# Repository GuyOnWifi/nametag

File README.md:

# Strawberry Badge

A little strawberry themed badge, with a microcontroller to control a bunch of LEDs. Twenty LEDs controlled by 5 GPIOs, what can go wrong? 

## BOM

| Designator | Footprint | Quantity | Value | LCSC Part # |
| --- | --- | --- | --- | --- |
| BT1 | BatteryHolder_Keystone_3034_1x20mm | 1 | Battery_Cell | C70376 |
| C1 | 0603 | 1 | 10pF | |
| C2 | 0603 | 1 | 100nF | |
| D1, D2, D3, D4, D5, D6, D7, D8, D9, D10, D12, D13, D15, D16, D17, D18, D19, D22 | 1206 | 18 | LED | |
| J1 | PinHeader_1x06_P2.54mm_Vertical | 1 | Conn_01x06_Pin | |
| R1, R2, R3, R4, R5 | 1206 | 5 | 330R | |
| R6 | 0603 | 1 | 10k | |
| U1 | QFN8P50_160X160X50L40X20N | 1 | NT3H2111W0FHK | C710403 |
| U2 | SOIC-8_5.3x5.3mm_P1.27mm | 1 | ATtiny85-20S | C89852 |

##

Slack Username: `Eason Huang`

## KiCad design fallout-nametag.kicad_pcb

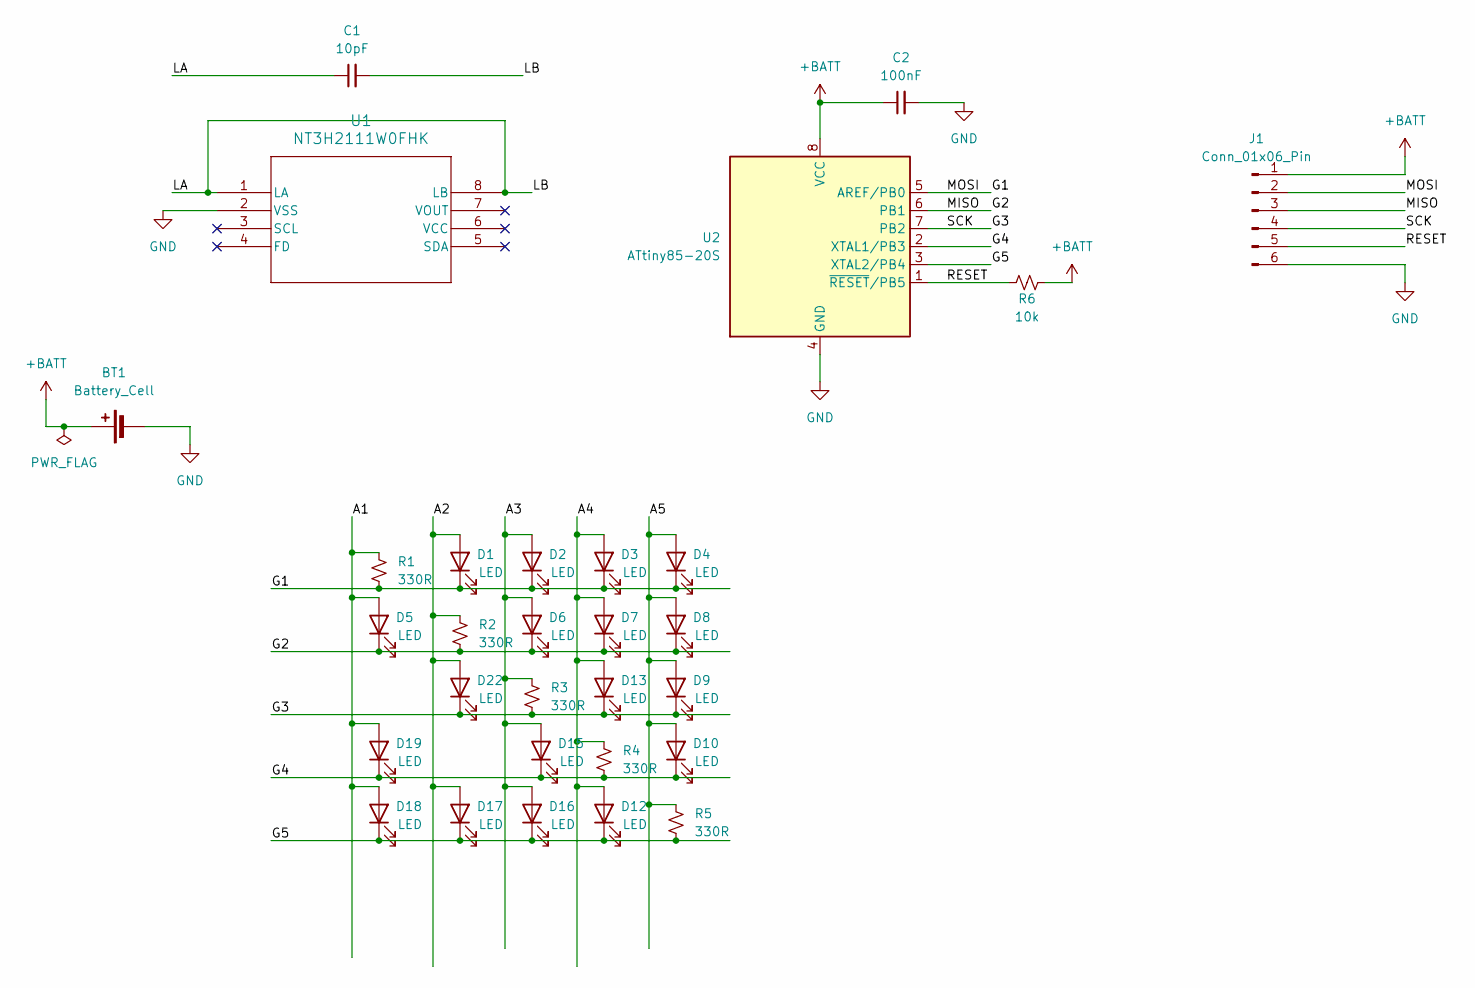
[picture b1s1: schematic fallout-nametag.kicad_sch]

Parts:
BT1: Battery_Cell; BatteryHolder_Keystone_3034_1x20mm
C1: 10pF; C_0603_1608Metric
C2: 100nF; C_0603_1608Metric
D1, D2, D3, D4, D5, D6, D7, D8, D9, D10, D12, D13, D15, D16, D17, D18, D19, D22: LED; LED_1206_3216Metric
J1: Conn_01x06_Pin; PinHeader_1x06_P2.54mm_Vertical
R1, R2, R3, R4, R5: 330R; R_1206_3216Metric
R6: 10k; R_0603_1608Metric
U1: NT3H2111W0FHK; QFN8P50_160X160X50L40X20N
U2: ATtiny85-20S; SOIC-8_5.3x5.3mm_P1.27mm

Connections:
+BATT: BT1.1 (+), C2.1, J1.1, R6.1, U2.8 (VCC)
/A1: D5.2 (A), D18.2 (A), D19.2 (A), R1.1
/A2: D1.2 (A), D17.2 (A), D22.2 (A), R2.1
/A3: D2.2 (A), D6.2 (A), D15.2 (A), D16.2 (A), R3.1
/A4: D3.2 (A), D7.2 (A), D12.2 (A), D13.2 (A), R4.1
/A5: D4.2 (A), D8.2 (A), D9.2 (A), D10.2 (A), R5.1
/G1: D1.1 (K), D2.1 (K), D3.1 (K), D4.1 (K), J1.2, R1.2, U2.5 (AREF/PB0)
/G2: D5.1 (K), D6.1 (K), D7.1 (K), D8.1 (K), J1.3, R2.2, U2.6 (PB1)
/G3: D9.1 (K), D13.1 (K), D22.1 (K), J1.4, R3.2, U2.7 (PB2)
/G4: D10.1 (K), D15.1 (K), D19.1 (K), R4.2, U2.2 (XTAL1/PB3)
/G5: D12.1 (K), D16.1 (K), D17.1 (K), D18.1 (K), R5.2, U2.3 (XTAL2/PB4)
/LA: C1.1, C1.2, U1.1 (LA), U1.8 (LB)
/RESET: J1.5, R6.2, U2.1 (~RESET/PB5)
GND: BT1.2 (-), C2.2, J1.6, U1.2 (VSS), U2.4 (GND)

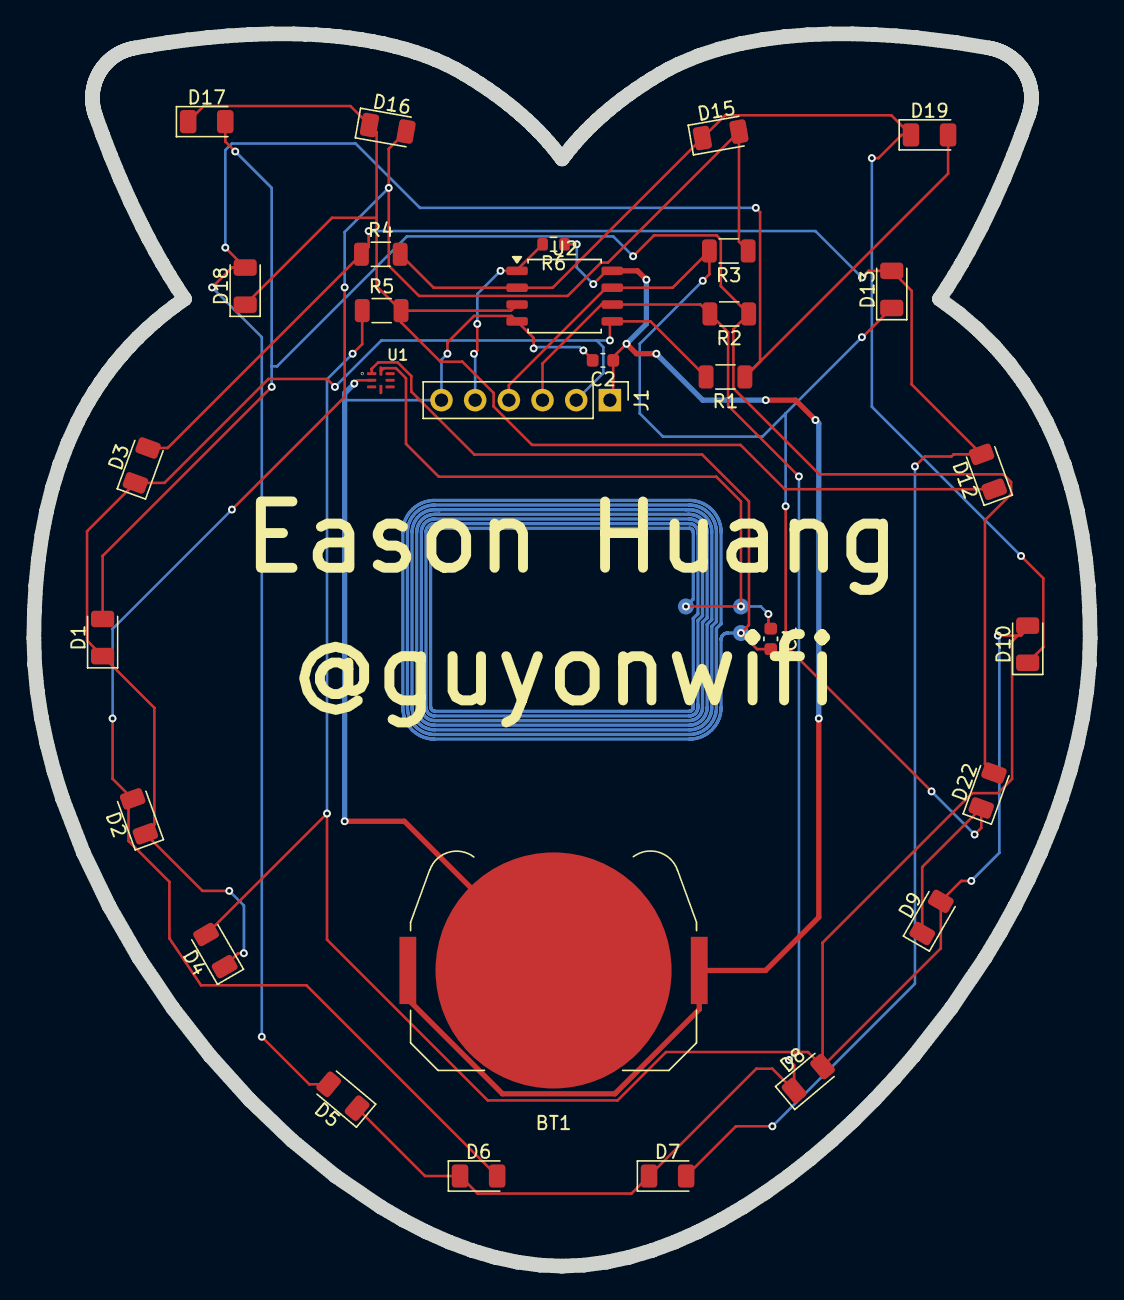
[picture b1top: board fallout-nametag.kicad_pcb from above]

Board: 2 copper layers, 79.6 x 92.9 mm, 30 parts (0 on the bottom side), 14 nets.

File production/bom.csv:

Designator,Footprint,Quantity,Value,LCSC Part #
BT1,BatteryHolder_Keystone_3034_1x20mm,1,Battery_Cell,
C1,0603,1,10pF,
C2,0603,1,100nF,
"D1, D10, D12, D13, D15, D16, D17, D18, D19, D2, D22, D3, D4, D5, D6, D7, D8, D9",1206,18,LED,
J1,PinHeader_1x06_P2.54mm_Vertical,1,Conn_01x06_Pin,
"R1, R2, R3, R4, R5",1206,5,330R,
R6,0603,1,10k,
U1,QFN8P50_160X160X50L40X20N,1,NT3H2111W0FHK,
U2,SOIC-8_5.3x5.3mm_P1.27mm,1,ATtiny85-20S,
